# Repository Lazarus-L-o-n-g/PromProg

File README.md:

# PromProg

PromProg is a versatile PROM Programmer for three basic PROM chips - 74188, 74S287 and 74S571.
Device is based on ATmega16 microcontroller, data for programming can be downloaded from master computer from your preferred terminal software in Intel HEX format or entered manually using keyboard. You can also read the content from chip and send it to the computer.

For powering use 15V/1A wall adapter or bench power supply.

More info at https://www.8bit-replicas.com/index.php/2021/08/26/programator-pamati-prom/

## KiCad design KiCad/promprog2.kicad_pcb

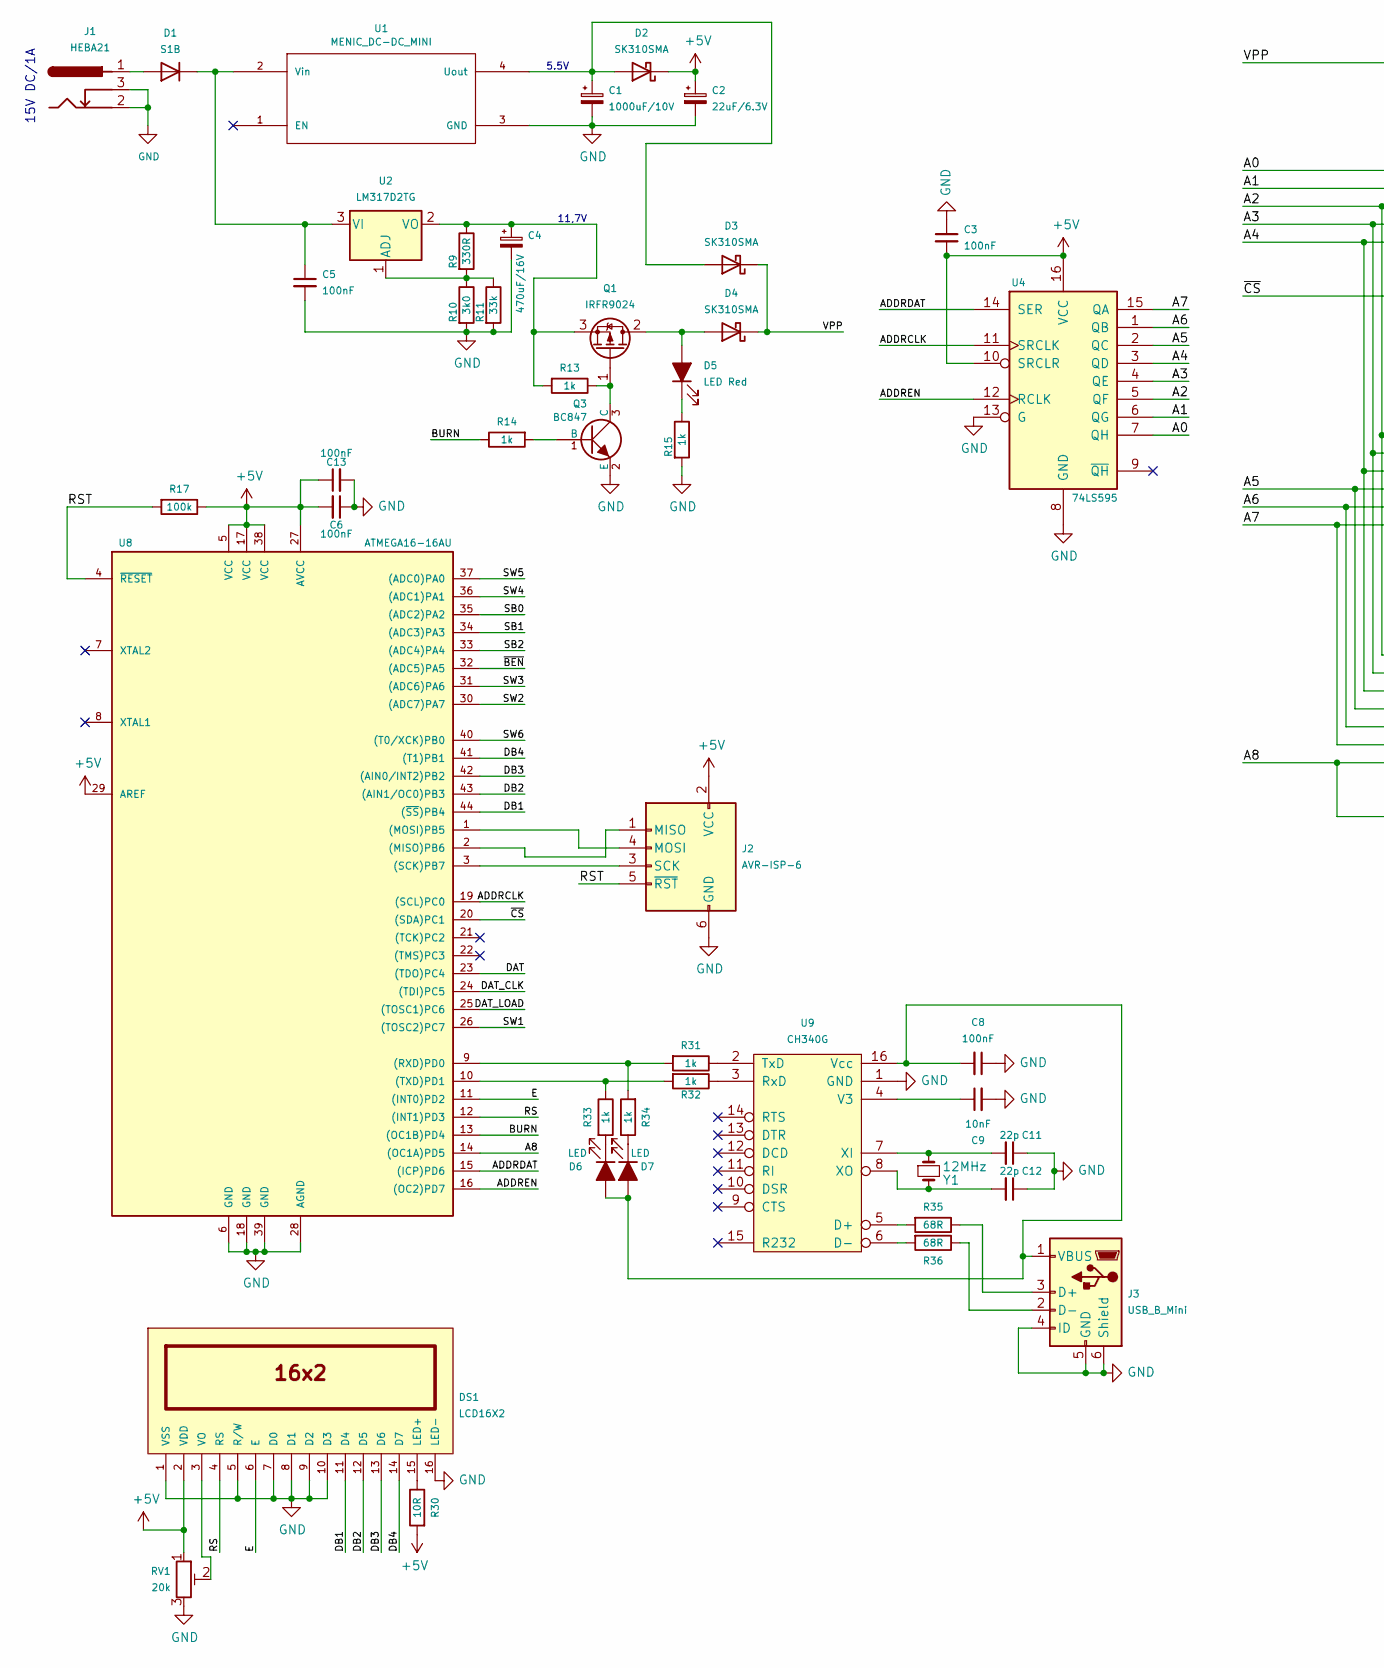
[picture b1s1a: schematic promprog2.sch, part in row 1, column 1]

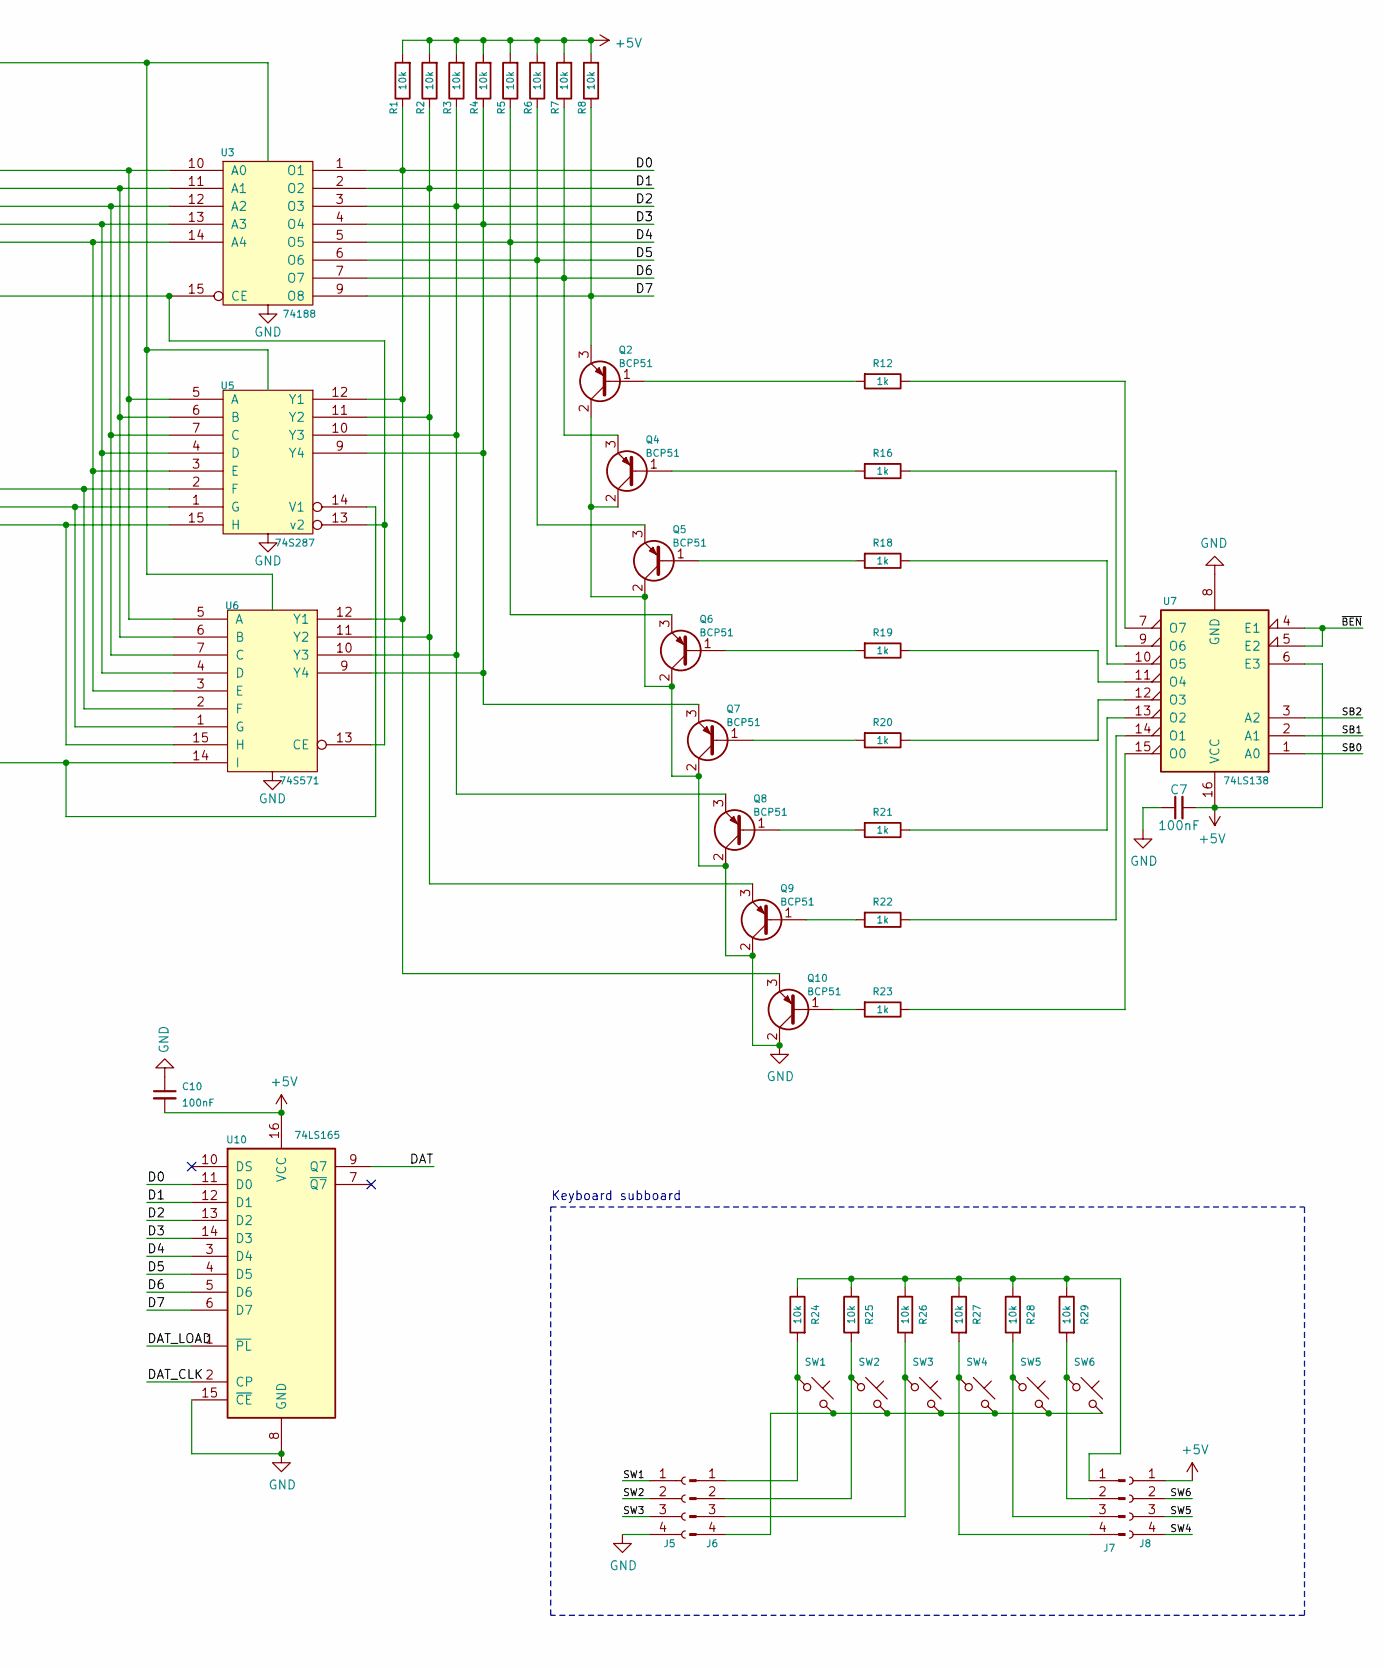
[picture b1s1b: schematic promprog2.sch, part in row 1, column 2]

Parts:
C1: 1000uF/10V; CP_Elec_10x10
C2: 22uF/6.3V; CP_EIA-3216-18_Kemet-A
C3, C5, C6, C7, C8, C10, C13: 100nF; C_1206_3216Metric_Pad1.24x1.80mm_HandSolder
C4: 470uF/16V; CP_Elec_8x10
C9: 10nF; C_1206_3216Metric_Pad1.24x1.80mm_HandSolder
C11, C12: 22p; C_1206_3216Metric_Pad1.24x1.80mm_HandSolder
D1: S1B; D_SMB_Handsoldering
D2, D3, D4: SK310SMA; D_SMA_Handsoldering
D5: LED Red; LED_D3.0mm
D6, D7: LED; LED_D3.0mm
DS1: LCD16X2; WC1602A
J1: HEBA21; BarrelJack_Horizontal
J2: AVR-ISP-6; PinHeader_2x03_P2.54mm_Vertical
J3: USB_B_Mini; USB_Mini-B_Lumber_2486_Horizontal
J5, J8: 4Pin F Header; PinSocket_1x04_P2.54mm_Vertical
J6, J7: 4Pin Header; PinHeader_1x04_P2.54mm_Vertical
Q1: IRFR9024; TO-252-3_TabPin2
Q2, Q4, Q5, Q6, Q7, Q8, Q9, Q10: BCP51; SOT-223-3_TabPin2
Q3: BC847; SOT-23_Handsoldering
R1, R2, R3, R4, R5, R6, R7, R8, R24, R25, R26, R27, R28, R29: 10k; R_1206_3216Metric_Pad1.24x1.80mm_HandSolder
R9: 330R; R_1206_3216Metric_Pad1.24x1.80mm_HandSolder
R10: 3k0; R_1206_3216Metric_Pad1.24x1.80mm_HandSolder
R11: 33k; R_1206_3216Metric_Pad1.24x1.80mm_HandSolder
R12, R13, R14, R15, R16, R18, R19, R20, R21, R22, R23, R31, R32, R33, R34: 1k; R_1206_3216Metric_Pad1.24x1.80mm_HandSolder
R17: 100k; R_1206_3216Metric_Pad1.24x1.80mm_HandSolder
R30: 10R; R_1206_3216Metric_Pad1.24x1.80mm_HandSolder
R35, R36: 68R; R_1206_3216Metric_Pad1.24x1.80mm_HandSolder
RV1: 20k; bourns_3364W
SW1, SW2, SW3, SW4, SW5, SW6: B3F-1052; SW_PUSH_6mm
U1: MENIC_DC-DC_MINI; DCDC_Small
U2: LM317D2TG; TO-263-3_TabPin2
U3: 74188; DIP-16_W7.62mm_LongPads
U4: 74LS595; SOIC-16_3.9x9.9mm_P1.27mm
U5: 74S287; DIP-16_W7.62mm_LongPads
U6: 74S571; DIP-16_W7.62mm_LongPads
U7: 74LS138; SOIC-16_3.9x9.9mm_P1.27mm
U8: ATMEGA16-16AU; TQFP-44_10x10mm_P0.8mm
U9: CH340G; SOIC-16_3.9x9.9mm_P1.27mm
U10: 74LS165; SOIC-16_3.9x9.9mm_P1.27mm
Y1: 12MHz; Crystal_SMD_HC49-SD_HandSoldering

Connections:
+5V: C2.1, C3.2, C6.2, C7.2, C10.2, C13.1, D2.1 (K), DS1.2 (VDD), J2.2 (VCC), J8.1, R1.2, R2.2, R3.2, R4.2, R5.2, R6.2, R7.2, R8.2, R17.1, R30.2, RV1.1, U4.10 (SRCLR), U4.16 (VCC), U7.6 (E3), U7.16 (VCC), U8.5 (VCC), U8.17 (VCC), U8.27 (AVCC), U8.29 (AREF), U8.38 (VCC), U10.16 (VCC)
/A0: U3.10 (A0), U4.7 (QH), U5.5 (A), U6.5 (A)
/A1: U3.11 (A1), U4.6 (QG), U5.6 (B), U6.6 (B)
/A2: U3.12 (A2), U4.5 (QF), U5.7 (C), U6.7 (C)
/A3: U3.13 (A3), U4.4 (QE), U5.4 (D), U6.4 (D)
/A4: U3.14 (A4), U4.3 (QD), U5.3 (E), U6.3 (E)
/A5: U4.2 (QC), U5.2 (F), U6.2 (F)
/A6: U4.1 (QB), U5.1 (G), U6.1 (G)
/A7: U4.15 (QA), U5.15 (H), U6.15 (H)
/A8: U5.14 (V1), U6.14 (I), U8.14 ((OC1A)PD5)
/ADDRCLK: U4.11 (SRCLK), U8.19 ((SCL)PC0)
/ADDRDAT: U4.14 (SER), U8.15 ((ICP)PD6)
/ADDREN: U4.12 (RCLK), U8.16 ((OC2)PD7)
/BURN: R14.1, U8.13 ((OC1B)PD4)
/D0: Q10.3 (E), R1.1, U3.1 (O1), U5.12 (Y1), U6.12 (Y1), U10.11 (D0)
/D1: Q9.3 (E), R2.1, U3.2 (O2), U5.11 (Y2), U6.11 (Y2), U10.12 (D1)
/D2: Q8.3 (E), R3.1, U3.3 (O3), U5.10 (Y3), U6.10 (Y3), U10.13 (D2)
/D3: Q7.3 (E), R4.1, U3.4 (O4), U5.9 (Y4), U6.9 (Y4), U10.14 (D3)
/D4: Q6.3 (E), R5.1, U3.5 (O5), U10.3 (D4)
/D5: Q5.3 (E), R6.1, U3.6 (O6), U10.4 (D5)
/D6: Q4.3 (E), R7.1, U3.7 (O7), U10.5 (D6)
/D7: Q2.3 (E), R8.1, U3.9 (O8), U10.6 (D7)
/DAT: U8.23 ((TDO)PC4), U10.9 (Q7)
/DAT_CLK: U8.24 ((TDI)PC5), U10.2 (CP)
/DAT_LOAD: U8.25 ((TOSC1)PC6), U10.1 (~PL)
/DB1: DS1.11 (D4), U8.44 ((~SS~)PB4)
/DB2: DS1.12 (D5), U8.43 ((AIN1/OC0)PB3)
/DB3: DS1.13 (D6), U8.42 ((AIN0/INT2)PB2)
/DB4: DS1.14 (D7), U8.41 ((T1)PB1)
/E: DS1.6 (E), U8.11 ((INT0)PD2)
/RS: DS1.4 (RS), U8.12 ((INT1)PD3)
/RST: J2.5 (~RST), R17.2, U8.4 (~RESET)
/SB0: U7.1 (A0), U8.35 ((ADC2)PA2)
/SB1: U7.2 (A1), U8.34 ((ADC3)PA3)
/SB2: U7.3 (A2), U8.33 ((ADC4)PA4)
/SW1: J5.1, U8.26 ((TOSC2)PC7)
/SW2: J5.2, U8.30 ((ADC7)PA7)
/SW3: J5.3, U8.31 ((ADC6)PA6)
/SW4: J8.4, U8.36 ((ADC1)PA1)
/SW5: J8.3, U8.37 ((ADC0)PA0)
/SW6: J8.2, U8.40 ((T0/XCK)PB0)
/VPP: D3.1 (K), D4.1 (K), U3.16 (Vcc), U5.16 (Vcc), U6.16 (Vcc)
/~BEN: U7.4 (E1), U7.5 (E2), U8.32 ((ADC5)PA5)
/~CS: U3.15 (CE), U5.13 (v2), U6.13 (CE), U8.20 ((SDA)PC1)
GND: C1.2, C2.2, C3.1, C4.2, C5.2, C6.1, C7.1, C8.1, C9.2, C10.1, C11.1, C12.1, C13.2, DS1.1 (VSS), DS1.5 (R/W), DS1.7 (D0), DS1.8 (D1), DS1.9 (D2), DS1.10 (D3), DS1.16 (LED-), J1.2, J1.3, J2.6 (GND), J3.4 (ID), J3.5 (GND), J3.6 (Shield), J5.4, Q2.2 (C), Q3.2 (E), Q4.2 (C), Q5.2 (C), Q6.2 (C), Q7.2 (C), Q8.2 (C), Q9.2 (C), Q10.2 (C), R10.2, R11.2, R15.2, RV1.3, U1.3 (GND), U3.8 (GND), U4.8 (GND), U4.13 (G), U5.8 (GND), U6.8 (GND), U7.8 (GND), U8.6 (GND), U8.18 (GND), U8.28 (AGND), U8.39 (GND), U9.1 (GND), U10.8 (GND), U10.15 (~CE)
unnamed: C1.1, D2.2 (A), D3.2 (A), U1.4 (Uout)
unnamed: C4.1, Q1.3 (S), R9.1, R13.2, U2.2 (VO)
unnamed: C5.1, D1.1 (K), U1.2 (Vin), U2.3 (VI)
unnamed: C8.2, D6.2 (A), D7.2 (A), J3.1 (VBUS), U9.16 (Vcc)
unnamed: C9.1, U9.4 (V3)
unnamed: C11.2, U9.7 (XI), Y1.1
unnamed: C12.2, U9.8 (XO), Y1.2
unnamed: D1.2 (A), J1.1
unnamed: D4.2 (A), D5.2 (A), Q1.2 (D)
unnamed: D5.1 (K), R15.1
unnamed: D6.1 (K), R33.2
unnamed: D7.1 (K), R34.1
unnamed: DS1.3 (VO), RV1.2
unnamed: DS1.15 (LED+), R30.1
unnamed: J2.1 (MISO), U8.2 ((MISO)PB6)
unnamed: J2.3 (SCK), U8.3 ((SCK)PB7)
unnamed: J2.4 (MOSI), U8.1 ((MOSI)PB5)
unnamed: J3.2 (D-), R36.1
unnamed: J3.3 (D+), R35.1
unnamed: J6.1, R24.2, SW1.1
unnamed: J6.2, R25.2, SW2.1
unnamed: J6.3, R26.2, SW3.1
unnamed: J6.4, SW1.2, SW2.2, SW3.2, SW4.2, SW5.2, SW6.2
unnamed: J7.1, R24.1, R25.1, R26.1, R27.1, R28.1, R29.1
unnamed: J7.2, R29.2, SW6.1
unnamed: J7.3, R28.2, SW5.1
unnamed: J7.4, R27.2, SW4.1
unnamed: Q1.1 (G), Q3.3 (C), R13.1
unnamed: Q2.1 (B), R12.2
unnamed: Q3.1 (B), R14.2
unnamed: Q4.1 (B), R16.2
unnamed: Q5.1 (B), R18.2
unnamed: Q6.1 (B), R19.2
unnamed: Q7.1 (B), R20.2
unnamed: Q8.1 (B), R21.2
unnamed: Q9.1 (B), R22.2
unnamed: Q10.1 (B), R23.2
unnamed: R9.2, R10.1, R11.1, U2.1 (ADJ)
unnamed: R12.1, U7.7 (O7)
unnamed: R16.1, U7.9 (O6)
unnamed: R18.1, U7.10 (O5)
unnamed: R19.1, U7.11 (O4)
unnamed: R20.1, U7.12 (O3)
unnamed: R21.1, U7.13 (O2)
unnamed: R22.1, U7.14 (O1)
unnamed: R23.1, U7.15 (O0)
unnamed: R31.1, U9.2 (TxD)
unnamed: R31.2, R34.2, U8.9 ((RXD)PD0)
unnamed: R32.1, U9.3 (RxD)
unnamed: R32.2, R33.1, U8.10 ((TXD)PD1)
unnamed: R35.2, U9.5 (D+)
unnamed: R36.2, U9.6 (D-)

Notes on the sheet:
15V DC/1A
11,7V
5.5V
Keyboard subboard

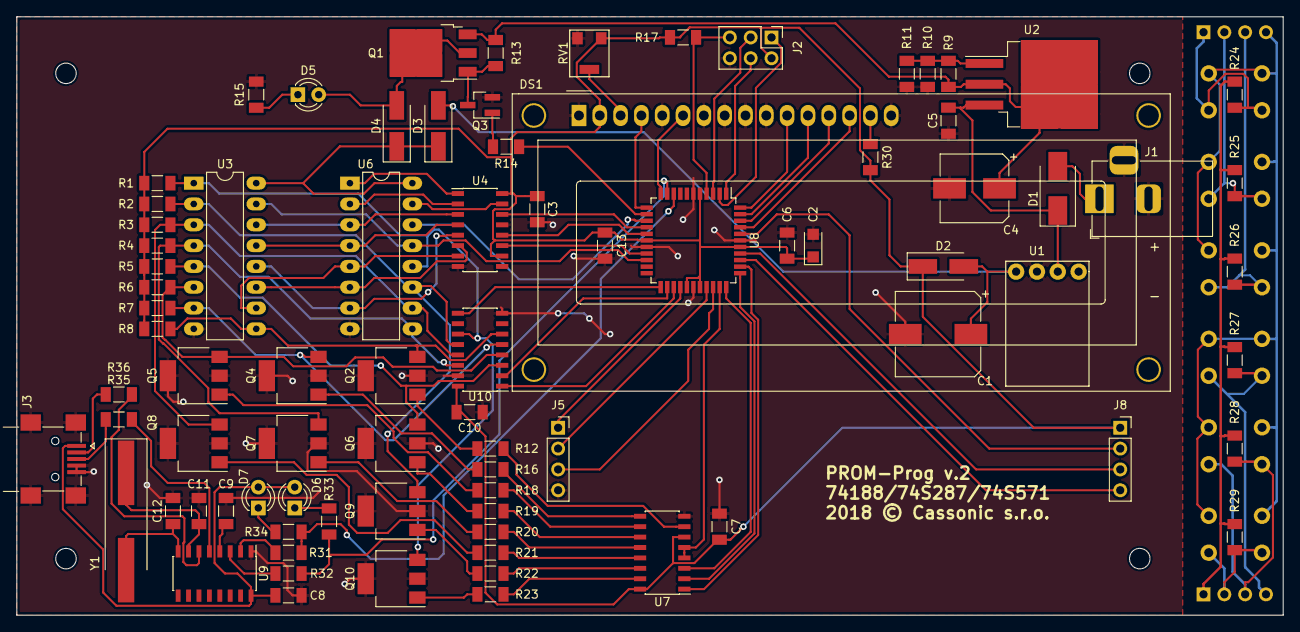
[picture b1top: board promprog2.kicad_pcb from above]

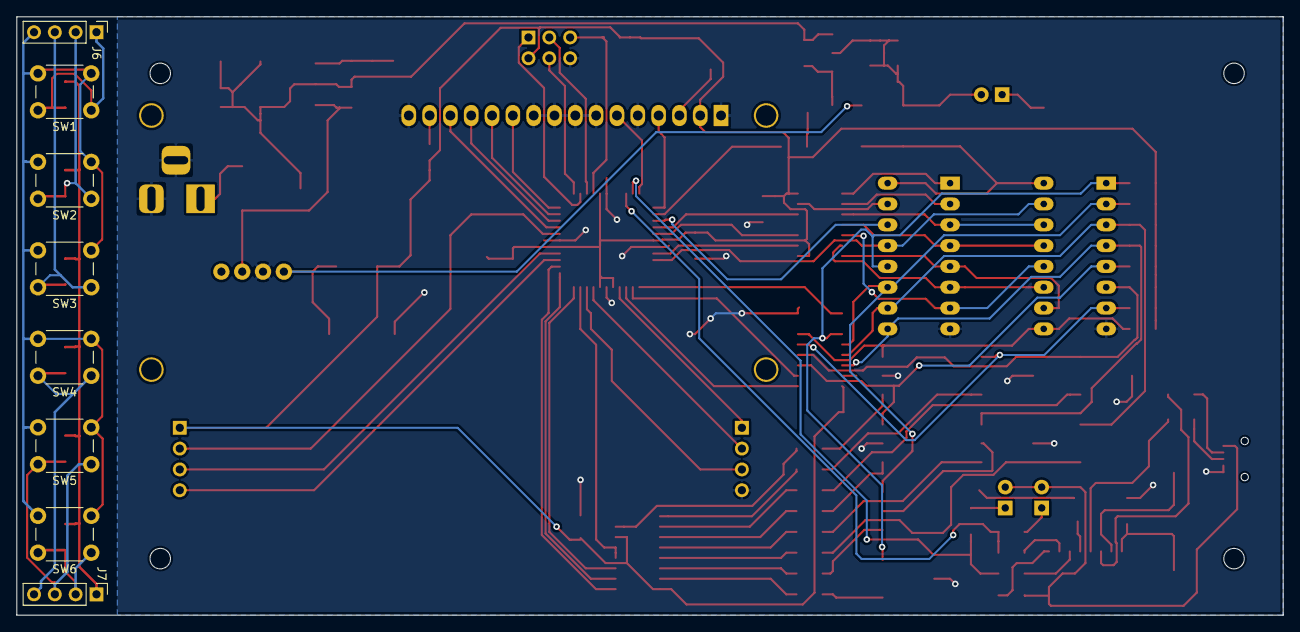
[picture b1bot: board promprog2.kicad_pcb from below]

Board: 2 copper layers, 154.5 x 73.0 mm, 95 parts (8 on the bottom side), 97 nets.

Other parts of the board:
H1, H2, H3, H4: MountingHole_2.5mm

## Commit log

2021-08-26 KiCad Files
2021-08-26 FreeCad and STL files for box
2021-08-26 Gerber files for PCB
2021-08-26 Firmware for microcontroller in Bascom
2021-08-26 BOM added
2021-08-26 PCB updated
2021-08-26 updated BOM
2021-11-11 fuses settings added
2022-08-24 New case design
2024-08-27 Software v1.2
    New version 1.2
    -Modified UI
    -Programming skips yet programmed bits
    -Programming check also the not-burned bits
    -New Verification function (usable as Blank check also)
    -Error counter could be more than 255 errors

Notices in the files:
KiCad/promprog2.kicad_pcb:
2018 © Cassonic s.r.o.
